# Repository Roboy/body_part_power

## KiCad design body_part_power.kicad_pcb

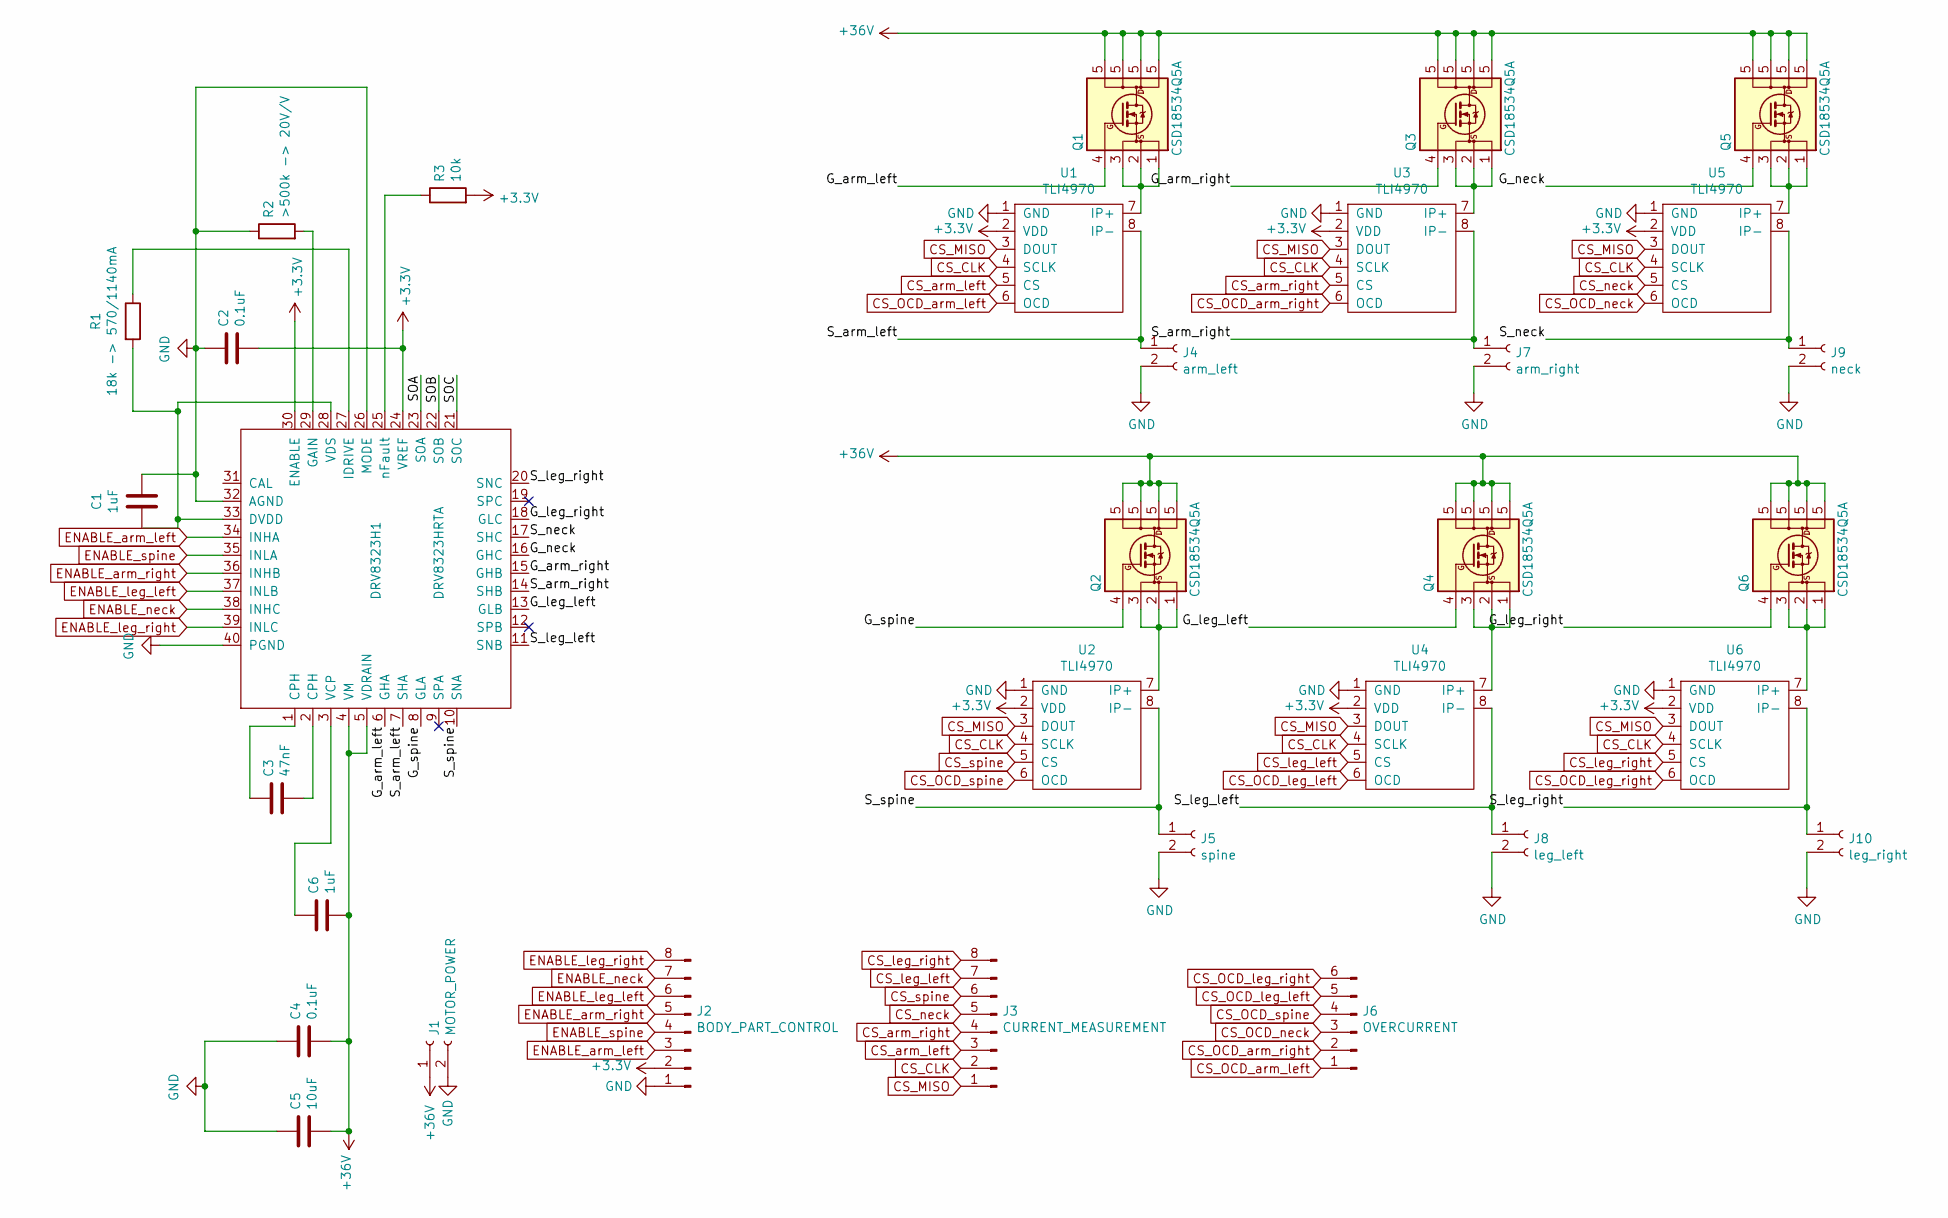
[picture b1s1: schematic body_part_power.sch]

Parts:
C1, C6: 1uF; C_0402_1005Metric
C2, C4: 0.1uF; C_0402_1005Metric
C3: 47nF; C_0402_1005Metric
C5: 10uF; C_0402_1005Metric
DRV8323H1: DRV8323HRTA; QFN-40-1EP_6x6mm_Pitch0.5mm
J1: MOTOR_POWER; Wago_2060_2_SMD
J2: BODY_PART_CONTROL; PinHeader_1x08_P2.54mm_Vertical
J3: CURRENT_MEASUREMENT; PinHeader_1x08_P2.54mm_Vertical
J4: arm_left; Wago_2060_2_SMD
J5: spine; Wago_2060_2_SMD
J6: OVERCURRENT; PinHeader_1x06_P2.54mm_Vertical
J7: arm_right; Wago_2060_2_SMD
J8: leg_left; Wago_2060_2_SMD
J9: neck; Wago_2060_2_SMD
J10: leg_right; Wago_2060_2_SMD
Q1, Q2, Q3, Q4, Q5, Q6: CSD18534Q5A; TDSON-8-1
R1: 18k -> 570/1140mA; R_0402_1005Metric
R2: >500k -> 20V/V; R_0402_1005Metric
R3: 10k; R_0402_1005Metric
U1, U2, U3, U4, U5, U6: TLI4970

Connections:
+3V3: C2.2, DRV8323H1.24 (VREF), DRV8323H1.30 (ENABLE), J2.2, R3.2, U1.2 (VDD), U2.2 (VDD), U3.2 (VDD), U4.2 (VDD), U5.2 (VDD), U6.2 (VDD)
+36V: C4.2, C5.2, C6.2, DRV8323H1.4 (VM), DRV8323H1.5 (VDRAIN), J1.1, Q1.5 (D), Q2.5 (D), Q3.5 (D), Q4.5 (D), Q5.5 (D), Q6.5 (D)
/G_arm_left: DRV8323H1.6 (GHA), Q1.4 (G)
/G_arm_right: DRV8323H1.15 (GHB), Q3.4 (G)
/G_leg_left: DRV8323H1.13 (GLB), Q4.4 (G)
/G_leg_right: DRV8323H1.18 (GLC), Q6.4 (G)
/G_neck: DRV8323H1.16 (GHC), Q5.4 (G)
/G_spine: DRV8323H1.8 (GLA), Q2.4 (G)
/SOA: DRV8323H1.23 (SOA)
/SOB: DRV8323H1.22 (SOB)
/SOC: DRV8323H1.21 (SOC)
/S_arm_left: DRV8323H1.7 (SHA), J4.1, U1.8 (IP-)
/S_arm_right: DRV8323H1.14 (SHB), J7.1, U3.8 (IP-)
/S_leg_left: DRV8323H1.11 (SNB), J8.1, U4.8 (IP-)
/S_leg_right: DRV8323H1.20 (SNC), J10.1, U6.8 (IP-)
/S_neck: DRV8323H1.17 (SHC), J9.1, U5.8 (IP-)
/S_spine: DRV8323H1.10 (SNA), J5.1, U2.8 (IP-)
CS_CLK: J3.2, U1.4 (SCLK), U2.4 (SCLK), U3.4 (SCLK), U4.4 (SCLK), U5.4 (SCLK), U6.4 (SCLK)
CS_MISO: J3.1, U1.3 (DOUT), U2.3 (DOUT), U3.3 (DOUT), U4.3 (DOUT), U5.3 (DOUT), U6.3 (DOUT)
CS_OCD_arm_left: J6.1, U1.6 (OCD)
CS_OCD_arm_right: J6.2, U3.6 (OCD)
CS_OCD_leg_left: J6.5, U4.6 (OCD)
CS_OCD_leg_right: J6.6, U6.6 (OCD)
CS_OCD_neck: J6.3, U5.6 (OCD)
CS_OCD_spine: J6.4, U2.6 (OCD)
CS_arm_left: J3.3, U1.5 (CS)
CS_arm_right: J3.4, U3.5 (CS)
CS_leg_left: J3.7, U4.5 (CS)
CS_leg_right: J3.8, U6.5 (CS)
CS_neck: J3.5, U5.5 (CS)
CS_spine: J3.6, U2.5 (CS)
ENABLE_arm_left: DRV8323H1.34 (INHA), J2.3
ENABLE_arm_right: DRV8323H1.36 (INHB), J2.5
ENABLE_leg_left: DRV8323H1.37 (INLB), J2.6
ENABLE_leg_right: DRV8323H1.39 (INLC), J2.8
ENABLE_neck: DRV8323H1.38 (INHC), J2.7
ENABLE_spine: DRV8323H1.35 (INLA), J2.4
GND: C1.1, C2.1, C4.1, C5.1, DRV8323H1.26 (MODE), DRV8323H1.32 (AGND), DRV8323H1.40 (PGND), J1.2, J2.1, J4.2, J5.2, J7.2, J8.2, J9.2, J10.2, R2.1, U1.1 (GND), U2.1 (GND), U3.1 (GND), U4.1 (GND), U5.1 (GND), U6.1 (GND)
unnamed: C1.2, DRV8323H1.28 (VDS), DRV8323H1.33 (DVDD), R1.2
unnamed: C3.1, DRV8323H1.1 (CPH)
unnamed: C3.2, DRV8323H1.2 (CPH)
unnamed: C6.1, DRV8323H1.3 (VCP)
unnamed: DRV8323H1.25 (nFault), R3.1
unnamed: DRV8323H1.27 (IDRIVE), R1.1
unnamed: DRV8323H1.29 (GAIN), R2.2
unnamed: Q1.1 (S), Q1.2 (S), Q1.3 (S), U1.7 (IP+)
unnamed: Q2.1 (S), Q2.2 (S), Q2.3 (S), U2.7 (IP+)
unnamed: Q3.1 (S), Q3.2 (S), Q3.3 (S), U3.7 (IP+)
unnamed: Q4.1 (S), Q4.2 (S), Q4.3 (S), U4.7 (IP+)
unnamed: Q5.1 (S), Q5.2 (S), Q5.3 (S), U5.7 (IP+)
unnamed: Q6.1 (S), Q6.2 (S), Q6.3 (S), U6.7 (IP+)

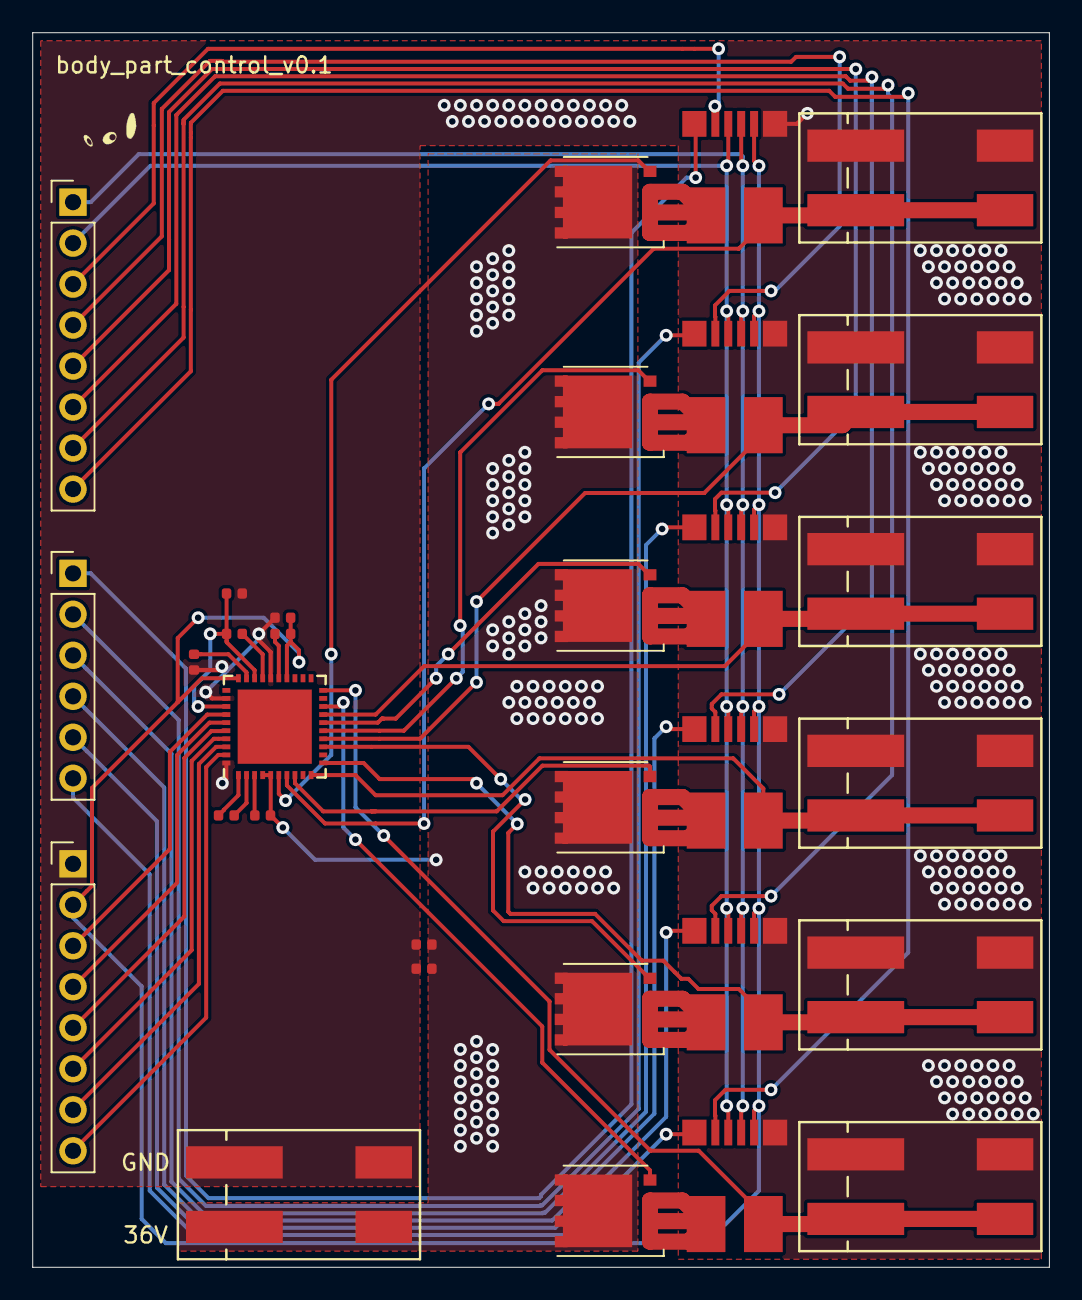
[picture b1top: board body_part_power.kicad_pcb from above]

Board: 2 copper layers, 63.0 x 76.5 mm, 32 parts (0 on the bottom side), 48 nets.

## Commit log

2019-08-04 orderd on pcbway
